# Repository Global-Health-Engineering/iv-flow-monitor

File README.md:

# Dripito — IV Drip Flow Monitor (Rev-B)

> Improving a low-cost intravenous infusion flow-rate monitoring device
> for paediatric care in humanitarian healthcare settings.
> ETH Zürich, Global Health Engineering — semester project, 2026.

A single-AA-cell IV drip monitor for resource-constrained clinical
environments. Custom STM32G0 PCB, optical dual-beam drop detection,
monochrome graphic LCD, piezo alarm, ASA-printed enclosure with
gear-driven broom-holder chamber clamp.

### → Full project page: **[gluflex.github.io/dripito](https://gluflex.github.io/dripito)**

Interactive dual-beam simulation, clickable PCB architecture, validation results, architecture decisions, assembly guide. This README covers only the essentials for cloning, building, and reproducing.

## At a glance

| | |
|---|---|
| **MCU** | STM32G071C8TX |
| **Hardware** | Rev-B PCB, KiCad 8.x, hand-assembled |
| **Detection** | Dual-beam optical, sphere-model volume calibration |
| **Power** | Single AA Li-ion via FFC, TPS610981 boost converter |
| **Enclosure** | ASA white FDM, sliding-gear chamber holder — Rev-B integrates the assembly for testing; full mechanical rework expected for Rev-C |
| **Validation** | 19 gravimetric-paired bench runs across 3 sessions (5 V_50 calibration + 11 position-drift + 3 raw-waveform-paired), macro-20 drip set; 7 raw-waveform captures total (4 unpaired warm-ups) |
| **BOM** | ~CHF 39, single-qty (see project page) |
| **Submission** | 2026-05-14 |

## Reproduce the analysis

One command, on a clean machine with Docker:

```bash
cd analysis/
docker compose up regenerate-figures-sample   # cold-clone test (sample data)
docker compose up regenerate-figures          # real campaign data
```

Pipeline source: [`analysis/notebooks/validation.ipynb`](analysis/notebooks/validation.ipynb).
Dependencies hash-locked in [`analysis/requirements.txt`](analysis/requirements.txt).
Protocol: [`docs/testing-and-validation.md`](docs/testing-and-validation.md).

## Build the firmware

1. Open `firmware/STM32CubeIDE/Dripito/` in STM32CubeIDE.
2. *Project → Build All*.
3. Connect ST-Link, *Run → Debug*.

Pin maps in [`firmware/README.md`](firmware/README.md).

## Hardware fabrication

PCB from `hardware/gerbers/` (JLCPCB / PCBWay).

Enclosure: STEP and STL exports in [`hardware/3dmodels/Enclosure/`](hardware/3dmodels/Enclosure/) (source CAD in Onshape). The current Rev-B enclosure is **not the final mechanical design** — it integrates the PCB + chamber holder + optics + battery into a testable assembly so the rest of the device can be validated. A full mechanical rework is expected for Rev-C. See [`docs/decisions/chamber-holder-mechanism.md`](docs/decisions/chamber-holder-mechanism.md), [`docs/decisions/sensor-arm-alignment.md`](docs/decisions/sensor-arm-alignment.md), and [`docs/enclosure-requirements.md`](docs/enclosure-requirements.md) for the rationale and Rev-C path.

## Repository layout

```
hardware/        KiCad 8.x project — schematic, PCB, libs, datasheets, gerbers, 3D models (PCB + Enclosure)
firmware/        STM32CubeIDE workspace (Dripito Rev-B)
enclosure/       Rev-B-is-not-final framing + cross-references; CAD lives in hardware/3dmodels/Enclosure/
docs/            Architecture decisions, requirements, results, limitations
data/            Raw validation CSVs, UART logs, gravimetric scale streams, geometry, edge cases
analysis/        Reproducible analysis pipeline (Docker + Jupyter) + diagnostic plotters + figures
tools/           Bench helpers (UART logging, scale logging, position-overlay rendering)
site/            GitHub Pages source (Astro)
media/           Photos, renders, demo clips
HANDOVER.md      State-of-the-prototype handover (Rev-B → Rev-C, what works / blockers / path)
CONTRIBUTING.md  Contribution guidelines (PRs paused during grading)
```

Each folder has its own `README.md`.

For the next person picking this up, start with [`HANDOVER.md`](HANDOVER.md): what works in Rev-B scope, the three blockers (position-dependence, drop-shape oscillation, tilt sensitivity), and the Rev-C optical-front-end path. [`docs/limitations.md`](docs/limitations.md) §17 is the matching architectural finding with bench evidence.

## Citation

A bachelor thesis preceded this work:

> Catarci, L. (2025). *Improving a Low-Cost Intravenous Infusion Flow-Rate Monitoring Device for Paediatric Care in Humanitarian Healthcare Settings*. ETH Zürich, Global Health Engineering. DOI: [10.5281/zenodo.16902366](https://doi.org/10.5281/zenodo.16902366).

The Rev-B work in this repository:

> Catarci, L. (2026). *Dripito — Open-Source IV Drip Flow Monitor (Rev-B)*. ETH Zürich, Global Health Engineering. DOI: [10.5281/zenodo.20199232](https://doi.org/10.5281/zenodo.20199232).

## License

- Code, firmware, docs, data: [CC BY 4.0](LICENSE-CC-BY-4.0.md)
- Hardware (KiCad project, custom symbols, most footprints): [CERN OHL 2.0 Permissive](LICENSE-CERN-OHL-2-PERMISSIVE.md)
- Three specific custom footprints: [CC BY-SA 4.0](LICENSE-CC-BY-SA-4.0.md) — see [`hardware/IV_Flow_Monitor_Footprints.pretty/README.md`](hardware/IV_Flow_Monitor_Footprints.pretty/README.md)
- CubeMX/HAL files retain `Copyright (c) STMicroelectronics` headers.

## Author and supervision

**Leandro Catarci** — MSc Mechanical Engineering, ETH Zürich. Semester project at ETH Global Health Engineering, 2026.

**Jakub Tkaczuk** — Supervisor.
**Prof. Elizabeth Tilley** — Group head, Chair of Global Health Engineering, ETH Zürich.

**Project originator:** Dr. Michelle Niescierenko — Boston Children's Hospital / Harvard Humanitarian Initiative.
**Clinical collaborator:** Dr. Janis Tupesis — University of Wisconsin / WHO Emergency Medical Teams.

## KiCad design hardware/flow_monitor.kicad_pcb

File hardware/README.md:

# hardware/

KiCad 8.x electronic design files for the Dripito monitor PCB —
schematic, board layout, project-local symbol and footprint libraries,
component datasheets, and fabrication outputs.

## Top-level files

| File | Purpose |
|------|---------|
| `flow_monitor.kicad_pro` | KiCad project file |
| `flow_monitor.kicad_sch` | Schematic |
| `flow_monitor.kicad_pcb` | Board layout |
| `sym-lib-table` | Registers `lib/IV_Flow_Monitor_Symbols.kicad_sym` |
| `fp-lib-table` | Registers `IV_Flow_Monitor_Footprints.pretty/` |
| `power_analysis.md` | Power-architecture analysis notes |

## Subdirectories

| Folder | Purpose |
|--------|---------|
| [`lib/`](lib/) | Project-local KiCad symbol libraries |
| [`IV_Flow_Monitor_Footprints.pretty/`](IV_Flow_Monitor_Footprints.pretty/) | Project-local KiCad footprint library |
| [`datasheets/`](datasheets/) | Component datasheets (PDFs) for everything on the BOM |
| [`gerbers/`](gerbers/) | Gerber + drill + pick-and-place fabrication outputs |
| [`3dmodels/`](3dmodels/) | 3D models (component STPs + assembled-board STEP exports) |
| [`scripts/`](scripts/) | Hardware-side automation (logo-to-footprint converter) |

## Gitignored paths

`flow_monitor-backups/` (KiCad timed snapshots), `temp/` (KiCad
scratch), `_autosave-*`, `fp-info-cache`.

## Workflow

- Open and build only via the **KiCad GUI** — no CLI build is configured.
- Hand-edits to `.kicad_sch` / `.kicad_pcb` (e.g. via scripts): always
  reopen in the KiCad GUI before committing — these files are sensitive
  to structural regressions that pass a text diff.
- New / copied symbols must have the project name in their `instances`
  block, or KiCad refuses to load them. Don't use `extends` inheritance
  across hierarchical `lib_symbols` blocks — flatten unit definitions.

## Licensing

- Three custom footprints are CC BY-SA 4.0 (see
  [`../LICENSE-CC-BY-SA-4.0.md`](../LICENSE-CC-BY-SA-4.0.md)):
  `SW_HYP_1TS005F-2500-5001`,
  `USB_C_Receptacle_GCT_USB4105-xx-A_16P_TopMnt_Horizontal`,
  `X_SW_Slide_SPDT_SSK12D07VG5`.
- All other hardware design files are CERN OHL 2.0 Permissive (see
  [`../LICENSE-CERN-OHL-2-PERMISSIVE.md`](../LICENSE-CERN-OHL-2-PERMISSIVE.md)).

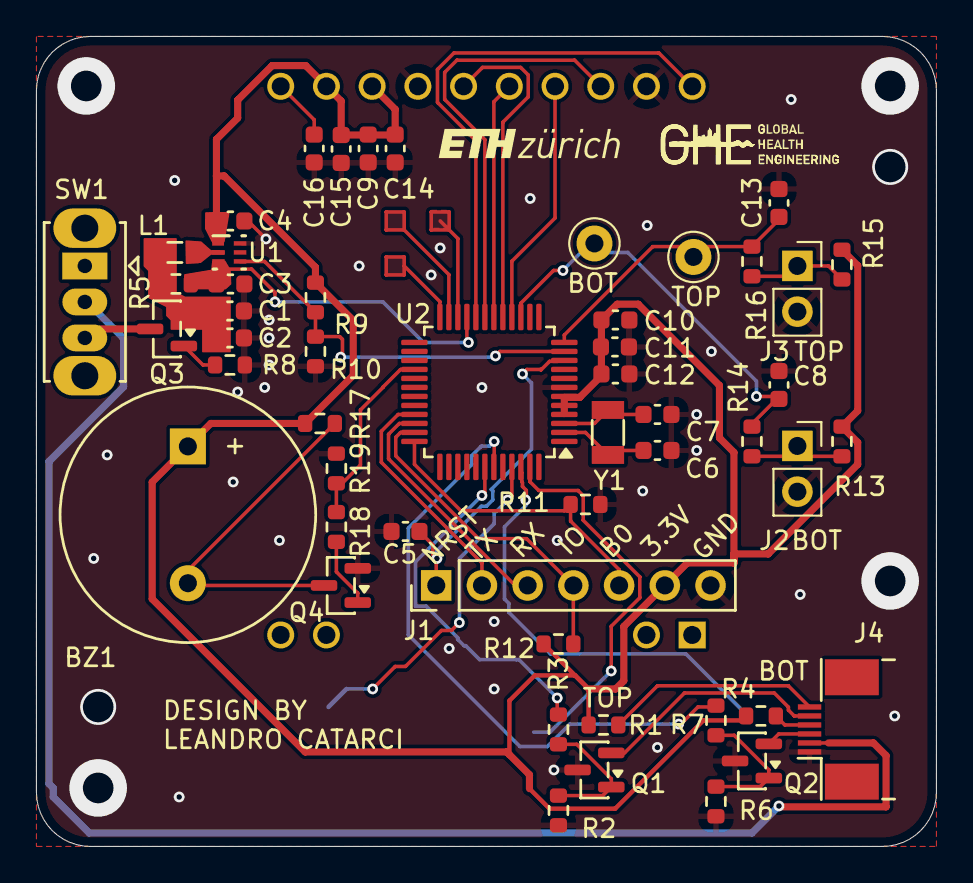
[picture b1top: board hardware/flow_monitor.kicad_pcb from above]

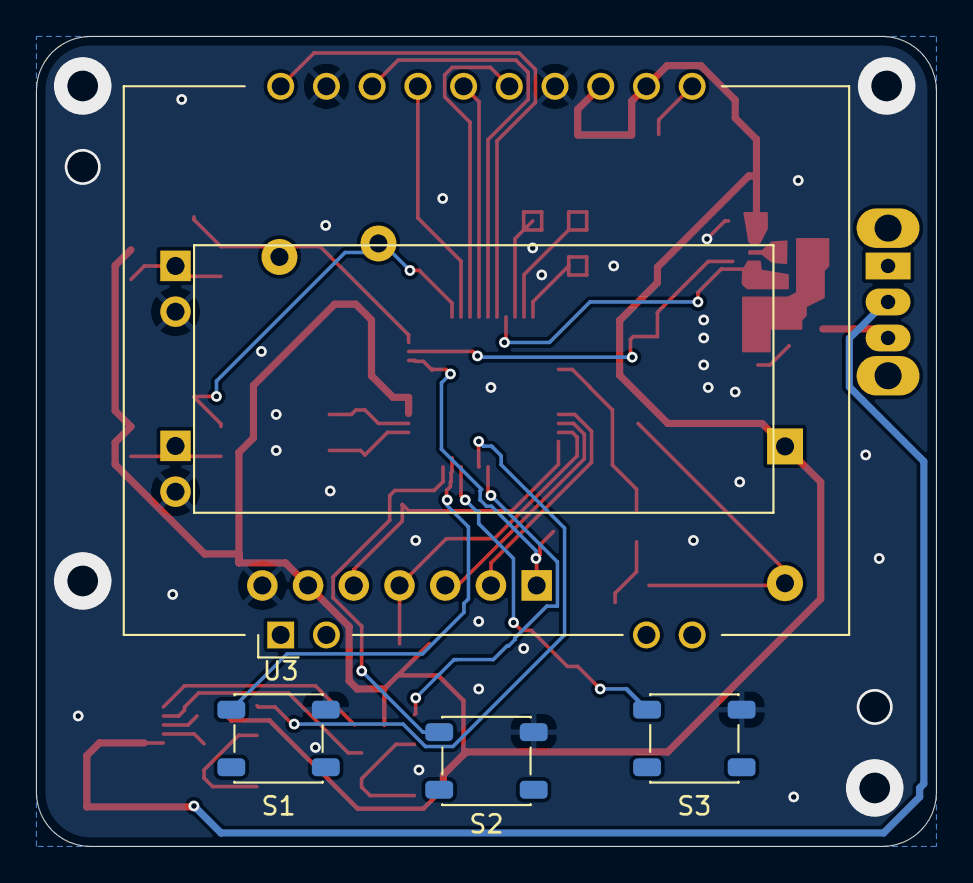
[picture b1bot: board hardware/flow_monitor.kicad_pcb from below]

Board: 2 copper layers, 50.0 x 45.0 mm, 55 parts (4 on the bottom side), 40 nets.

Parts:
BOT: TestPoint; TestPoint_Keystone_5000-5004_Miniature
BZ1: SFN-1407PA7.6; Buzzer_S&S_SFN-1407PA7.6
C1: 10uF; C_0603_1608Metric
C2, C3, C5, C14: 100nF; C_0603_1608Metric
C4: 22uF; C_0603_1608Metric
C6, C7: 20pF; C_0603_1608Metric
C8, C13: 100pF; C_0603_1608Metric
C9, C10, C12: 0.1uF; C_0603_1608Metric
C11: 1uF; C_0603_1608Metric
C15: 4700nF; C_0603_1608Metric
C16: 1000nF; C_0603_1608Metric
J1: Conn_01x07_Pin; PinHeader_1x07_P2.54mm_Vertical
J2: Conn_01x02_Socket_TOP; PinSocket_1x02_P2.54mm_Vertical
J3: Conn_01x02_Socket_BOT; PinSocket_1x02_P2.54mm_Vertical
J4: Conn_01x06_Socket; Jushuo_AFC07-S06FCA-00_1x6-1MP_P0.50_Horizontal
L1: 4.7uH; L_0805_2012Metric
Q1, Q2, Q4: 2N7002; SOT-23
Q3: AO3401A; SOT-23
R1, R3, R4, R7, R14, R16, R18: 100Ω; R_0603_1608Metric
R2, R6: 100kΩ; R_0603_1608Metric
R5: 390Ohm; R_0603_1608Metric
R8, R9, R10: 100k; R_0603_1608Metric
R11, R12, R19: 10kΩ; R_0603_1608Metric
R13, R15: 3.3kΩ; R_0603_1608Metric
R17: 1800Ω; R_0603_1608Metric
S1, S2, S3: PTS647SN38SMTR2_LFS; SW_SPST_PTS647_Sx38
SW1: SK12D07VG5; X_SW_Slide_SPDT_SSK12D07VG5
TP1: TestPoint; TestPoint_Keystone_5000-5004_Miniature
U1: TPS610981DSET; DSE0006A
U2: STM32G071C8Tx; LQFP-48_7x7mm_P0.5mm
U3: EA_DOGS164W-A; EA_DOGS164X-A
Y1: Crystal; Crystal_SMD_3215-2Pin_3.2x1.5mm

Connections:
+3.3V: BZ1.1 (+), C4.2, C9.1, C10.1, C11.2, C12.2, C14.1, C15.2, J1.6, R1.1, R4.1, R9.1, R12.1, R13.1, R15.1, R17.1, U1.1 (VMAIN), U2.4 (VBAT), U2.5 (VREF+), U2.6 (VDD), U3.12 (IM1), U3.13 (VDD)
/BUZZER_GATE: Q4.1 (G), R18.1
/LCD_VOUT: C16.2, U3.11 (VOUT)
/LED_GATE_BOT: Q2.1 (G), R6.2, R7.1
/LED_GATE_TOP: Q1.1 (G), R2.2, R3.1
/OSC32_IN: C6.2, U2.2 (PC14), Y1.2
/OSC32_OUT: C7.2, U2.3 (PC15), Y1.1
ADC_IR_DETECTOR_BOT: BOT.1, C8.2, R14.1, U2.15 (PA4)
ADC_IR_DETECTOR_TOP: C13.2, R16.1, TP1.1, U2.12 (PA1)
ADC_V_BAT: C3.2, R5.2, U1.3 (VIN), U2.21 (PB2)
BAT+: J4.2, SW1.2 (B)
BOOT0: J1.5, R11.1, U2.36 (PA14)
BST_MODE: R9.2, R10.1, U1.4 (MODE), U2.11 (PA0)
BST_SW: L1.2, U1.2 (SW)
BTN_MODE: S1.1 (NO), U2.46 (PB7)
BTN_MUTE: S3.1 (NO), U2.45 (PB6)
BTN_RES: S2.1 (NO), U2.47 (PB8)
BUZZER_CTRL: R18.2, R19.2, U2.28 (PA8)
BZ_DRN: BZ1.2 (-), Q4.3 (D), R17.2
GND: C1.2, C2.1, C3.1, C4.1, C5.2, C6.1, C7.1, C8.1, C9.2, C10.2, C11.1, C12.1, C13.1, C14.2, C15.1, C16.1, J1.7, J2.2, J3.2, J4.1, Q1.3 (D), Q2.3 (D), Q4.2 (S), R2.1, R6.1, R8.2, R10.2, R11.2, R19.1, S1.1 (NO), S2.1 (NO), S3.1 (NO), U1.6 (GND), U2.7 (VSS), U3.14 (VSS), U3.19 (SA0)
IR_LED_BOT+: J4.4, R4.2
IR_LED_BOT-: J4.3, Q2.2 (S)
IR_LED_TOP+: J4.6, R1.2
IR_LED_TOP-: J4.5, Q1.2 (S)
LCD_CS: U2.19 (PB0), U3.18 (CS)
LCD_MISO: U2.17 (PA6), U3.15 (SOD)
LCD_MOSI: U2.18 (PA7), U3.16 (SID)
LCD_RST: U2.20 (PB1), U3.20 (RST)
LCD_SCK: U2.16 (PA5), U3.17 (SCLK)
LED_CTRL_BOT: R7.2, U2.43 (PB4)
LED_CTRL_TOP: R3.2, U2.42 (PB3)
NRST: C5.1, J1.1, U2.10 (NRST)
PD_BIAS_BOT: J2.1, R13.2, R14.2
PD_BIAS_TOP: J3.1, R15.2, R16.2
RPOL_GATE: Q3.1 (G), R8.1
SWDIO: J1.4, R12.2, U2.35 (PA13)
UART1_RX: J1.3, U2.34 (PA10/PA12)
UART1_TX: J1.2, U2.33 (PA9/PA11)
VBAT_PROT: C1.1, C2.2, L1.1, Q3.2 (S), R5.1
VBAT_SW: Q3.3 (D), SW1.3 (C)

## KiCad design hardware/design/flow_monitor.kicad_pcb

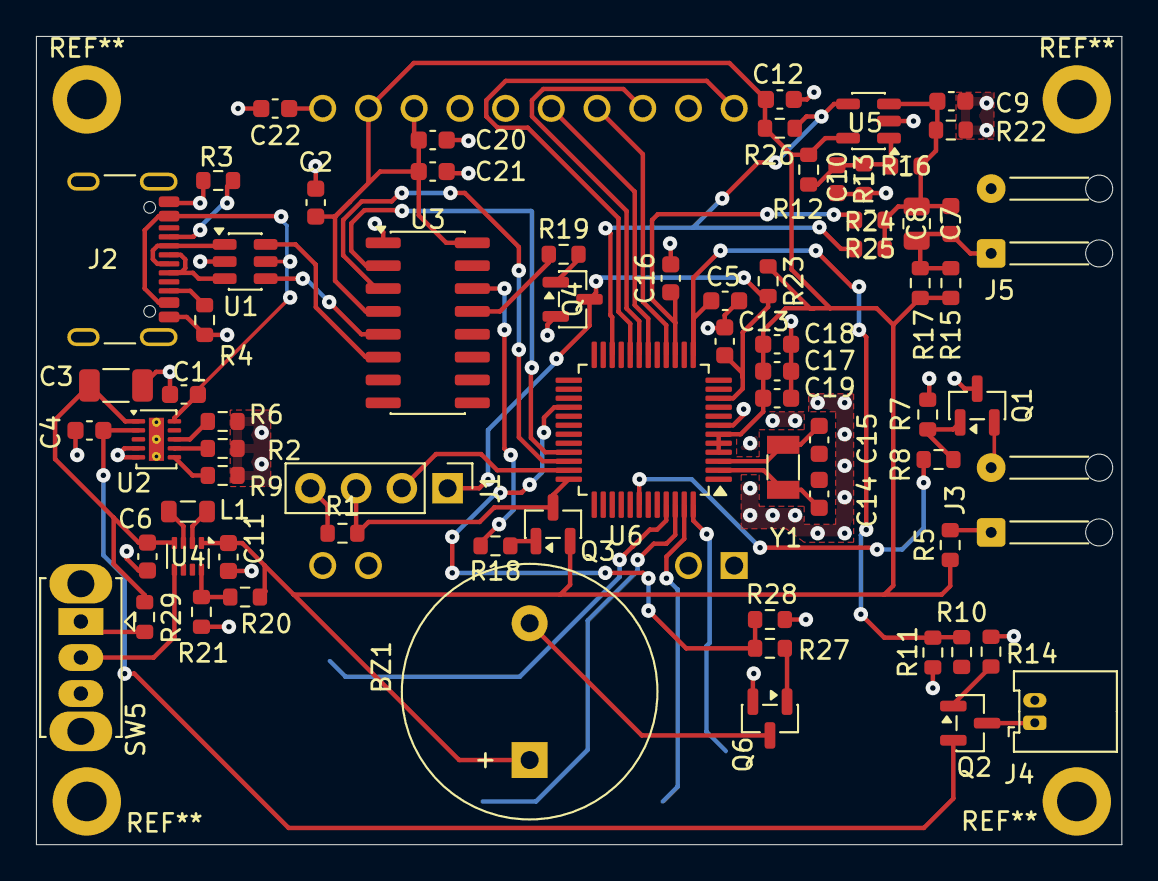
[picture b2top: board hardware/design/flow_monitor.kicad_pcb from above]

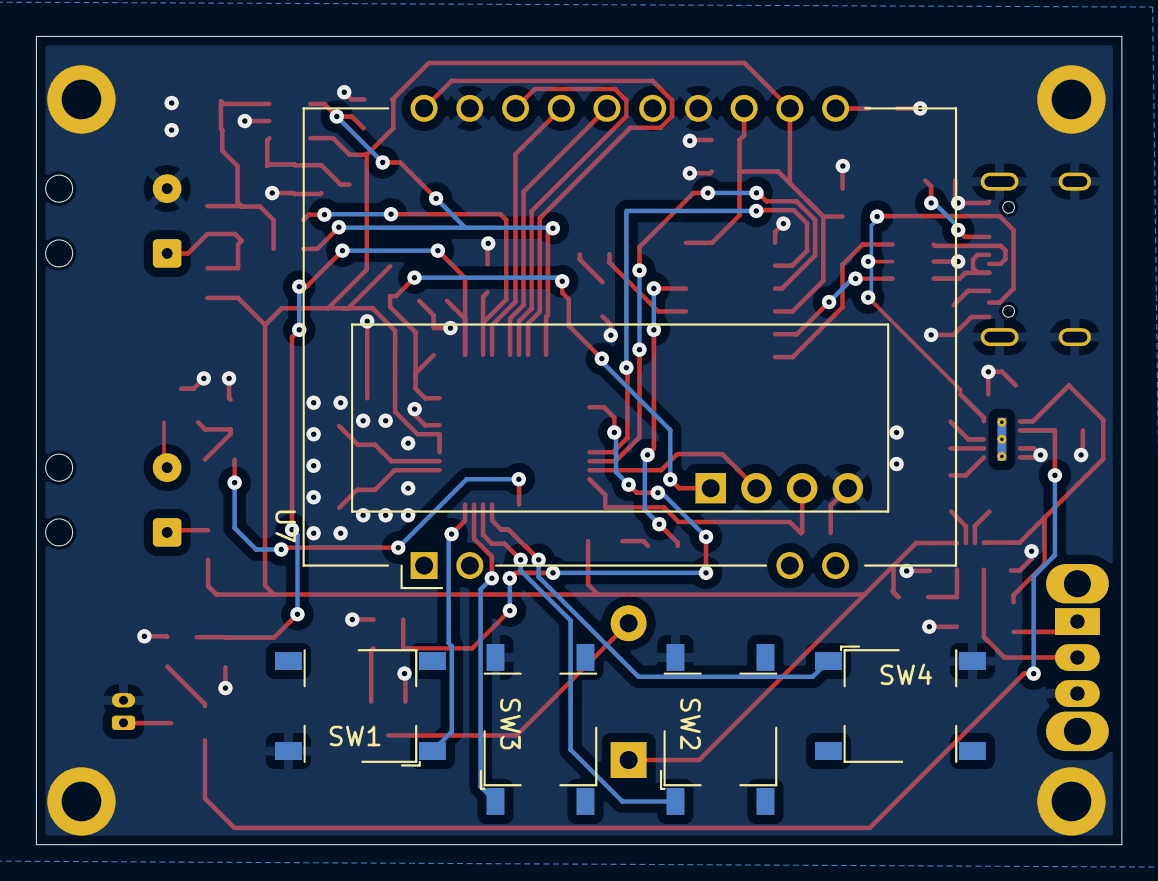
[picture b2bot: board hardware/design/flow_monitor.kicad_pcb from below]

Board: 2 copper layers, 60.3 x 44.9 mm, 76 parts (5 on the bottom side), 54 nets.

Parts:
BZ1: SFN-1407PA7.6; Buzzer_S&S_SFN-1407PA7.6
C1, C4: 1uF; C_0603_1608Metric
C2, C5, C7, C9, C10, C12, C16, C20: 100nF; C_0603_1608Metric
C3: 10uF; C_1206_3216Metric
C6, C11: 22uF; C_0603_1608Metric
C8: 4700nF; C_0805_2012Metric
C13, C17, C19: 0.1mF; C_0603_1608Metric
C14, C15: 20pF; C_0603_1608Metric
C18: 1mF; C_0603_1608Metric
C21: 4700nF; C_0603_1608Metric
C22: 1000nF; C_0603_1608Metric
J1: Conn_01x04_Pin; PinHeader_1x04_P2.54mm_Vertical
J2: USB_C_Receptacle_USB2.0_16P; USB_C_Receptacle_GCT_USB4105-xx-A_16P_TopMnt_Horizontal
J3, J5: Conn_01x02_Socket; SolderWire-0.1sqmm_1x02_P3.6mm_D0.4mm_OD1mm_Relief
J4: Conn_01x02_Socket; Molex_PicoBlade_53048-0210_1x02_P1.25mm_Horizontal
L1: 1uL; L_0805_2012Metric
Q1, Q6: 2N7002; SOT-23
Q2: IRLML6402; SOT-23
Q3: BC807; SOT-23
Q4: BC817; SOT-23
R1, R9, R14, R15, R18, R19, R23, R26, R28, R29: 10kΩ; R_0603_1608Metric
R2: 18kΩ; R_0603_1608Metric
R3, R4: 5.1kΩ; R_0603_1608Metric
R5, R8, R24, R27: 100Ω; R_0603_1608Metric
R6: 1kΩ; R_0603_1608Metric
R7: 100kΩ; R_0603_1608Metric
R10, R16, R22: 1MΩ; R_0603_1608Metric
R11: 500kΩ; R_0603_1608Metric
R12, R13: 47kΩ; R_0603_1608Metric
R17: 3.3kΩ; R_0603_1608Metric
R20: 511kΩ; R_0603_1608Metric
R21: 91kΩ; R_0603_1608Metric
R25: 330kΩ; R_0603_1608Metric
SW1, SW2, SW3, SW4: 1TS005F-2500-5001; SW_HYP_1TS005F-2500-5001
SW5: SW_SPDT; UNFINIDHED_SW_Slide_SPDT_SSK12D07VG5
U1: USBLC6-2SC6; SOT-23-6
U2: BQ25185DLHR; WSON-10-1EP_2x3mm_P0.5mm_EP0.84x2.4mm_ThermalVias
U3: CH340C; SOIC-16_3.9x9.9mm_P1.27mm
U4: TPS631000; SOT-583-8
U5: LMV331; SOT-23-5
U6: STM32G030C8Tx; LQFP-48_7x7mm_P0.5mm
U7: EA_DOGS164W-A; EA_DOGS104X-A
Y1: Crystal; Crystal_SMD_3215-2Pin_3.2x1.5mm

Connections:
+3.3V: BZ1.1 (+), C2.1, C11.2, C12.2, C17.1, C18.2, C19.2, C20.1, C21.2, Q3.2 (E), R5.1, R12.1, R15.1, R17.1, R20.1, R23.1, R26.1, U3.4 (V3), U3.16 (VCC), U4.1 (VOUT), U5.5 (V+), U6.4 (VBAT), U6.5 (VREF+), U6.6 (VDD), U7.12 (IM1), U7.13 (VDD)
+5V: C1.2, J2.A4 (VBUS), J2.A9 (VBUS), J2.B4 (VBUS), J2.B9 (VBUS), U1.5 (VBUS), U2.10 (IN)
/BAT+: J4.1, Q2.3 (D)
/BUZZER_GATE: Q6.1 (G), R27.1
/IR_LED+: J3.1, R5.2
/IR_LED-: J3.2, Q1.2 (S)
/LCD_VOUT: C22.2, U7.11 (VOUT)
/LED_GATE: Q1.1 (G), R7.2, R8.1
/OSC32_IN: C14.2, U6.2 (PC14), Y1.2
/OSC32_OUT: C15.2, U6.3 (PC15), Y1.1
/PD_AC: C7.1, C8.1, C9.2, R16.1, R22.1, R24.2, R25.1, U5.3 (-)
/PD_K: C7.2, C8.2, J5.1, R15.2, R17.2
/VREF = 1.65V: C10.2, R12.2, R13.1, R16.2, U5.1 (+)
ADC_IR_DETECTOR: C16.2, R24.1, U6.15 (PA4)
ADC_V_BAT: C5.1, R10.2, R11.1, U6.13 (PA2)
BOOT0: J1.3, Q3.3 (C), R1.1, U6.36 (PA14)
BTN_MINUS: SW1.1, U6.48 (PB9)
BTN_MODE: SW2.1, U6.46 (PB7)
BTN_MUTE: SW4.1, U6.45 (PB6)
BTN_PLUS: SW3.1, U6.47 (PB8)
BUZZER_CTRL: R27.2, R28.2, U6.28 (PA8)
DROP_INT: R25.2, R26.2, U5.4, U6.22 (PB10)
GND: C1.1, C2.2, C3.1, C4.1, C5.2, C6.1, C9.1, C10.1, C11.1, C12.1, C13.1, C14.1, C15.1, C16.1, C17.2, C18.1, C19.1, C20.2, C21.1, C22.1, J1.4, J2.A1 (GND), J2.A12 (GND), J2.B1 (GND), J2.B12 (GND), J2.SH, J4.2, J5.2, Q1.3 (D), Q4.2 (E), Q6.2 (S), R1.2, R2.1, R3.1, R4.2, R6.1, R7.1, R9.1, R11.2, R13.2, R14.2, R21.2, R22.2, R28.1, SW1.2, SW2.2, SW3.2, SW4.2, SW5.3 (C), U1.2 (GND), U2.4 (CE), U2.5 (GND), U3.1 (GND), U4.6 (MODE), U4.7 (GND), U5.2 (V-), U6.7 (VSS), U7.14 (VSS), U7.19 (SA0)
LCD_CS: U6.19 (PB0), U7.18 (CS)
LCD_MOSI: U6.18 (PA7), U7.16 (SID)
LCD_RST: U6.20 (PB1), U7.20 (RST)
LCD_SCK: U6.16 (PA5), U7.17 (SCLK)
LED_CTRL: R8.2, U6.42 (PB3)
NRST: C13.2, J1.1, Q4.3 (C), R23.2, U6.10 (NRST)
unnamed: BZ1.2 (-), Q6.3 (D)
unnamed: J2.A5 (CC1), R3.2
unnamed: J2.B5 (CC2), R4.1
unnamed: J2.A6 (D+), J2.B6 (D+), U1.3 (I/O2)
unnamed: J2.A7 (D-), J2.B7 (D-), U1.1 (I/O1)
unnamed: Q2.1 (G), R14.1
unnamed: C4.2, Q2.2 (S), R10.1, U2.2 (BAT)
unnamed: Q3.1 (B), R18.1
unnamed: Q4.1 (B), R19.2
unnamed: R29.1, SW5.1 (A)
unnamed: SW5.2 (B), U4.5 (EN)
unnamed: R2.2, U2.7 (ILIM/VSET)
unnamed: R6.2, U2.8 (ISET)
unnamed: C3.2, C6.2, R29.2, U2.1 (SYS), U4.4 (VIN)
unnamed: R9.2, U2.6 (TS/MR)
unnamed: R20.2, R21.1, U4.8 (FB)
unnamed: L1.1, U4.3 (LX1)
unnamed: L1.2, U4.2 (LX2)
SWDIO: J1.2, U6.35 (PA13)
UART1_RX: U3.3 (RXD), U6.34 (PA10/PA12)
UART1_TX: U3.2 (TXD), U6.33 (PA9/PA11)
UART_DTR: R19.1, U3.13 (~DTR)
UART_RTS: R18.2, U3.14 (~RTS)
USB_D+: U1.4 (I/O2), U3.5 (UD+)
USB_D-: U1.6 (I/O1), U3.6 (UD-)

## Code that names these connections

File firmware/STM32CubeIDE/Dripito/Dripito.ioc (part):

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Mcu.Name=STM32G071C(6-8-B)Tx
Mcu.Package=LQFP48
Mcu.UserName=STM32G071C8Tx
PA0.GPIOParameters=GPIO_Label
PA0.GPIO_Label=BST_MODE
PA0.Signal=GPIO_Output
PA1.GPIOParameters=GPIO_Label
PA1.GPIO_Label=ADC_IR_DETECTOR_TOP
PA1.Signal=SharedAnalog_PA1
PA10.GPIOParameters=GPIO_Label
PA10.GPIO_Label=UART1_RX
PA10.Mode=Asynchronous
PA10.Signal=USART1_RX
PA13.Mode=Serial_Wire
PA13.Signal=SYS_SWDIO
PA14-BOOT0.Mode=Serial_Wire
PA14-BOOT0.Signal=SYS_SWCLK
PA4.GPIOParameters=GPIO_Label
PA4.GPIO_Label=ADC_IR_DETECTOR_BOT
PA4.Mode=IN4
PA4.Signal=ADC1_IN4
PA5.GPIOParameters=GPIO_Label
PA5.GPIO_Label=LCD_SCK
PA5.Mode=Full_Duplex_Master
PA5.Signal=SPI1_SCK
PA6.GPIOParameters=GPIO_Label
PA6.GPIO_Label=LCD_MISO
PA6.Mode=Full_Duplex_Master
PA6.Signal=SPI1_MISO
PA7.GPIOParameters=GPIO_Label
PA7.GPIO_Label=LCD_MOSI
PA7.Mode=Full_Duplex_Master
PA7.Signal=SPI1_MOSI
PA8.GPIOParameters=GPIO_Label
PA8.GPIO_Label=BUZZER_CTRL
PA8.Signal=S_TIM1_CH1
PA9.GPIOParameters=GPIO_Label
PA9.GPIO_Label=UART1_TX
PA9.Mode=Asynchronous
PA9.Signal=USART1_TX
PB0.GPIOParameters=GPIO_Label
PB0.GPIO_Label=LCD_CS
PB0.Signal=GPIO_Output
PB1.GPIOParameters=GPIO_Label
PB1.GPIO_Label=LCD_RST
PB1.Signal=GPIO_Output
PB2.GPIOParameters=GPIO_Label
PB2.GPIO_Label=ADC_V_BAT
PB2.Mode=IN10
PB2.Signal=ADC1_IN10
PB3.GPIOParameters=GPIO_Label
PB3.GPIO_Label=LED_CTRL_TOP
PB3.Signal=S_TIM1_CH2
PB4.GPIOParameters=GPIO_Label
PB4.GPIO_Label=LED_CTRL_BOT
PB4.Signal=GPIO_Output
PB6.GPIOParameters=GPIO_PuPd,GPIO_Label
PB6.GPIO_Label=BTN_MUTE
PB6.GPIO_PuPd=GPIO_PULLUP
PB6.Signal=GPIO_Input
PB7.GPIOParameters=GPIO_PuPd,GPIO_Label
PB7.GPIO_Label=BTN_MODE
PB7.GPIO_PuPd=GPIO_PULLUP
PB7.Signal=GPIO_Input
PB8.GPIOParameters=GPIO_Label
PB8.GPIO_Label=BTN_RES
PB8.Signal=GPIO_Input
PC14-OSC32_IN\ (PC14).GPIOParameters=GPIO_Label
PC14-OSC32_IN\ (PC14).GPIO_Label=OSC32_IN
PC14-OSC32_IN\ (PC14).Mode=LSE-External-Oscillator
PC14-OSC32_IN\ (PC14).Signal=RCC_OSC32_IN
PC15-OSC32_OUT\ (PC15).GPIOParameters=GPIO_Label
PC15-OSC32_OUT\ (PC15).GPIO_Label=OSC32_OUT
PC15-OSC32_OUT\ (PC15).Mode=LSE-External-Oscillator
PC15-OSC32_OUT\ (PC15).Signal=RCC_OSC32_OUT
RCC.HSE_VALUE=8000000
RCC.SYSCLKFreq_VALUE=64000000
RCC.SYSCLKSource=RCC_SYSCLKSOURCE_PLLCLK
board=custom

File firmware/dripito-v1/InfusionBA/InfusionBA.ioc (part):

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Mcu.Name=STM32G030C(6-8)Tx
Mcu.Package=LQFP48
Mcu.UserName=STM32G030C8Tx
PA13.Mode=Serial_Wire
PA13.Signal=SYS_SWDIO
PA14-BOOT0.Mode=Serial_Wire
PA14-BOOT0.Signal=SYS_SWCLK
PA15.Mode=Asynchronous
PA15.Signal=USART2_RX
PA2.GPIOParameters=GPIO_Label
PA2.GPIO_Label=LOG_TX
PA2.Mode=Asynchronous
PA2.Signal=USART2_TX
PA3.GPIOParameters=GPIO_Label
PA3.GPIO_Label=PD_ADC
PA3.Mode=IN3
PA3.Signal=ADC1_IN3
PA4.Mode=IN4
PA4.Signal=ADC1_IN4
PA5.GPIOParameters=GPIO_Label
PA5.GPIO_Label=LCD_SCK
PA5.Mode=TX_Only_Simplex_Unidirect_Master
PA5.Signal=SPI1_SCK
PA7.GPIOParameters=GPIO_Label
PA7.GPIO_Label=LCD_MOSI
PA7.Mode=TX_Only_Simplex_Unidirect_Master
PA7.Signal=SPI1_MOSI
PA8.Signal=S_TIM1_CH1
PB0.GPIOParameters=GPIO_Speed,GPIO_PuPd,GPIO_Label,GPIO_ModeDefaultOutputPP
PB0.GPIO_Label=LCD_CS
PB0.GPIO_ModeDefaultOutputPP=GPIO_MODE_OUTPUT_PP
PB0.GPIO_PuPd=GPIO_PULLUP
PB0.GPIO_Speed=GPIO_SPEED_FREQ_HIGH
PB0.Signal=GPIO_Output
PB1.GPIOParameters=GPIO_Speed,GPIO_PuPd,GPIO_Label,GPIO_ModeDefaultOutputPP
PB1.GPIO_Label=LCD_RST
PB1.GPIO_ModeDefaultOutputPP=GPIO_MODE_OUTPUT_PP
PB1.GPIO_PuPd=GPIO_NOPULL
PB1.GPIO_Speed=GPIO_SPEED_FREQ_MEDIUM
PB1.Signal=GPIO_Output
PB10.GPIOParameters=GPIO_Label,GPIO_ModeDefaultEXTI
PB10.GPIO_Label=DROP_INT
PB10.GPIO_ModeDefaultEXTI=GPIO_MODE_IT_FALLING
PB10.Signal=GPXTI10
PB12.GPIOParameters=GPIO_Speed,PinState,GPIO_Label
PB12.GPIO_Label=BOOST_MODE_CTRL
PB12.GPIO_Speed=GPIO_SPEED_FREQ_MEDIUM
PB12.PinState=GPIO_PIN_SET
PB12.Signal=GPIO_Output
PB3.GPIOParameters=GPIO_Label
PB3.GPIO_Label=LED_CTRL
PB3.Signal=S_TIM1_CH2
PB6.GPIOParameters=GPIO_PuPd,GPIO_Label
PB6.GPIO_Label=BTN_MINUS
PB6.GPIO_PuPd=GPIO_PULLUP
PB6.Signal=GPIO_Input
PB7.GPIOParameters=GPIO_PuPd,GPIO_Label
PB7.GPIO_Label=BTN_PLUS
PB7.GPIO_PuPd=GPIO_PULLUP
PB7.Signal=GPIO_Input
PB8.GPIOParameters=GPIO_PuPd,GPIO_Label
PB8.GPIO_Label=BTN_MODE
PB8.GPIO_PuPd=GPIO_PULLUP
PB8.Signal=GPIO_Input
PB9.GPIOParameters=GPIO_PuPd,GPIO_Label
PB9.GPIO_Label=BTN_MUTE
PB9.GPIO_PuPd=GPIO_PULLUP
PB9.Signal=GPIO_Input
PC14-OSC32_IN\ (PC14).GPIOParameters=GPIO_Label
PC14-OSC32_IN\ (PC14).GPIO_Label=OSC32_IN
PC14-OSC32_IN\ (PC14).Mode=LSE-External-Oscillator
PC14-OSC32_IN\ (PC14).Signal=RCC_OSC32_IN
PC15-OSC32_OUT\ (PC15).GPIOParameters=GPIO_Label
PC15-OSC32_OUT\ (PC15).GPIO_Label=OSC32_OUT
PC15-OSC32_OUT\ (PC15).Mode=LSE-External-Oscillator
PC15-OSC32_OUT\ (PC15).Signal=RCC_OSC32_OUT
RCC.HSE_VALUE=8000000
RCC.SYSCLKFreq_VALUE=64000000
RCC.SYSCLKSource=RCC_SYSCLKSOURCE_PLLCLK
board=custom

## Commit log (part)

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2025-06-24 Add Altium IV_INFUSION_BA project files
2025-06-24 Add .gitignore to clean STM32CubeIDE and build files
2025-06-24 Fixed Logging (Hardware Issue: connect TX of Dripito with TX of ST-Link, NOT RX). Added Serial Logging for each button.
2025-06-25 Working Cursor Blinking
2025-08-03 fix(lcd): correct SPI nibble order and dial contrast • DOGS164 shows text now
2025-08-03 Resolve merge conflict: combine lcd.h and main.c
2025-08-03 Fixed Missing Functions
2025-08-03 Switch to external oscillator
2025-08-03 Set default target rate to 100 mL/h and add button hold
2025-08-03 Revert Back to old oscillator
2025-08-03 Fix button handling and flow simulation
2025-08-03 Implement flow and stop alarms with mute control
2025-08-04 Remove simulated drop and toggle display
2025-08-04 fixed press and hold on plus and minus button.
2025-08-04 Tried to fix battery, didn't work
2025-08-07 Deactivated Alarm
2025-08-19 Upload Analysis from Drive to Github
2026-02-18 cleanup
2026-02-27 final upload
2026-03-06 udpate doi
2026-03-14 Added MISO routing to LCD Screen
2026-03-20 add source and results at glance
2026-05-04 Add Rev-B hardware and firmware baseline
    - InfusionBA2: new STM32G071 project for Rev-B (dual photodiode, LPTIM1 Phase 2)
    - KiCad: Rev-B schematic + PCB (DOGS164, G071, TPS610981, COMP1 simplification)
    - Gerbers + STEP files from JLCPCB order W2026040304309275
    - Logo footprints (ETH, GHE) and generation script
    - Remove stale KiCad backup zips and lock files
2026-05-05 docs(testing): add pre-registered validation protocol
    Imports the EXP-0 through EXP-6 validation protocol from the working
    notes into the repository as a standalone, version-controlled document.
    This commit's timestamp serves as the pre-registration mark for the
    2026-05-07 → 2026-05-10 validation campaign — the protocol exists in
    git history before any official data is collected.
    Includes:
2026-05-05 docs(analysis): scaffold analysis/ with reproducibility contract
    Stub analysis/ with a README documenting the layout (notebooks/,
    figures/, scripts/), the pinning policy (requirements.in →
    requirements.txt via pip-compile, Dockerfile with digest-pinned base),
    and the reproducibility contract: a single command regenerates every
    figure from raw CSVs.
    Three reproduction paths documented for different audiences:
2026-05-05 docs(enclosure): add hand-off requirements spec for follow-up thesis
    Add docs/enclosure-requirements.md as a written specification for the
    3D-printed casing, pitched explicitly at a successor MSc/BSc student
    or a Rev-C revision. Captures *what the enclosure must do* once,
    durably, so the next revision does not re-derive these from clinical
    interviews and supplier catalogues.
    Sections:
2026-05-05 docs(media): document naming, formats, and what does not belong here
    Replace the one-line README with a useful one. Documents the naming
    convention (kebab-case for stable assets, YYYY-MM-DD prefix for dated
    shots, _render suffix to disambiguate renders from photos), format /
    resolution policy (max edge 2048 px, JPEG/PNG/MP4 by content type),
    and an explicit "what does not belong here" list.
    Specifically routes:
2026-05-07 chore(hardware): drop generated PCB and schematic review JSONs
2026-05-07 docs(testing): drop pre-registration framing, keep methodological discipline
2026-05-08 feat(led): drive LED_TOP at 100% duty
    Bump TIM1_CH2 compare from 125 (~50% duty) to 250 (compare > ARR=249,
    output always active). Equalises LED_TOP drive with LED_BOT (which is
    GPIO held HIGH = 100%) so steady-state ADC readings on the two channels
    become directly comparable for the asymmetry investigation logged in
    the journal entry today.
2026-05-12 feat(site): vendor Astro site source and add GitHub Pages deploy workflow
    Move the standalone Astro source from ../pages-astro/ into site/ so the
    GitHub Pages deploy runs from this repo. Workflow triggers on push to v2
    when site/** changes (plus workflow_dispatch). astro.config.mjs already
    targets gluflex.github.io/iv-flow-monitor-v2 — no config change needed.
    Post-merge, one manual step: Settings → Pages → Source → "GitHub Actions"
    to enable the deploy.
2026-05-14 fix(site): repoint every broken Pages link to real GitHub URLs
    The Pages site is an Astro single-page app under site/; it does not
    render docs/*.md. Every link to /docs/<anything>, every href="#"
    anchor, and the Decisions cards (pointing at a non-existent main
    branch) were 404. This commit repoints all of them to the GitHub
    blob/v2 / tree/v2 URLs that actually resolve. The two pages that
    genuinely don't exist (recommendations.html, external-reproducibility)
2026-05-14 feat(site): add Open Graph + Twitter Card + canonical + favicon
    The site shipped with bare title/description meta and no favicon.
    Sharing the URL on Slack/email/Twitter produced no preview. Adds
    absolute-URL canonical link, an SVG favicon, og:type/url/title/
    description/image/site_name, and matching Twitter summary_large_image
    tags. OG image reuses the existing PCB top render under site/public/pcb/.
2026-05-14 feat(site): make BOM groups collapsible (compact by default)
    Bill of materials previously rendered all 39 line items expanded —
    visually overwhelming for a glance. Now each group (Main PCB,
    Satellite breakout, Mechanical) collapses by default. Default view
    shows only the group headers, group subtotals, and the grand total
    (7 rows total). Clicking a group header expands or collapses just its
    line items; a new 'Expand all / Collapse all' pill in the header
2026-05-14 docs(analysis): drop AI-flavoured "the contract" sentence from README opener
    Sentence read as marketing rather than documentation; the section heading "Reproducing the analysis" already conveys the same idea without the rhetorical flourish.
2026-05-14 refactor(site): drop "Status" cell from Assembly manifest header
    Status meta-cell ("Bench-ready / Step N next / Build complete") was redundant — Steps counter + progress bar already convey the same state. Removes the third manifest cell, the related CSS, and the J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
2026-05-14 fix(site): Hero — drop stale STM32G0 + CHF 50 line, replace DOI badge with snapshot tag
    Third sentence ("Built on STM32G0, ≤ CHF 50 BOM target, deployable without an infusion pump") removed: STM32G0 is implementation detail that belongs in PCB section, and CHF 50 is the original target 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
2026-05-14 fix(site): PCB Hotspot 3 — Phase 1 LEDs are always-on continuous, not 8.3% duty
    Firmware confirms (main.c:395-398): TIM1_CH2 PWM at 100% duty for LED_TOP, static GPIO high for LED_BOT — both LEDs always on at ~21 mA each in Phase 1 active monitoring. The 8.3% / 150 µs / 1.80 ms 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
2026-05-14 chore(site): remove PowerTree component from PCB section
    PowerTree.astro had stale Li-ion AA framing, wrong Phase 1 duty (8.3 % → actually 100 %), and an aspirational ≥14 days runtime target that doesn't match any honest current number. The DualBeam.astro 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
2026-05-14 fix(site): use :global() for chime button so Astro doesn't hash the inner selector
    Previous fix .play-sound-slot button still got compiled to .play-sound-slot[data-astro-cid] button[data-astro-cid] — the inner button still required the scoping attribute, which the innerHTML-injecte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
2026-05-14 docs(results): tighten + honest-frame headline; cut drop-shape, op-envelope, V_50_05 sections
    Reframed headline: ±30 % per-run spread is far outside any clinical
    accuracy target — Rev-B is a dual-beam architecture demonstrator, not a
    clinically deployable monitor. Removed the "fundamental limit of the
    chord-time architecture" defence wording.
    Cut three sections that diluted the main story without adding load-bearing
    evidence: Architecture finding 3 (drop-shape oscillation deep-dive),
2026-05-14 chore(site): remove Pause/Step controls from DualBeam — sim auto-runs
    The Pause/Step controls in the DualBeam interactive existed mainly for
    debugging the per-drop animation. They cluttered the controls strip
    without serving the reader, who just wants to see the visualisation
    behave correctly at a chosen drip rate.
    Removed:
    - the two buttons from the controls strip
2026-05-14 docs(site): remove sanity-check bench figures from Analysis section
    Cumulative-mass and TOP-velocity-histogram figures were sanity-checks
    of the bench protocol, not findings of architectural significance.
    The architectural findings list right below already carries the
    analytical conclusions; the protocol-sanity panels added length
    without changing any reader's understanding of the device.
    Removed both figures plus the "figures below sanity-check the bench
2026-05-14 fix(site): let Reproducibility prose span the full panel width
    Removed the 70ch / 78ch max-width caps on .reproducibility p and
    .reproducibility p.repro-foot. The paragraphs were rendering as a narrow
    left-aligned column even though the panel container was wide, leaving a
    visually unbalanced right margin. Lines now run to the panel edge,
    matching the width of the <pre> code blocks.
2026-05-14 docs(site): relocate raw-waveform position figures to Analysis; drop confusing 3-session Bland-Altman
    Three changes:
    1. Cross-session Bland-Altman figure removed from Limitations §17.
    "One V_CAL_K, three sessions, one image" was technically the
    cleanest summary of position-dependence, but the n=737/n=150/n=51
    overlay with three different bias bands made the reader work too
    hard for the takeaway.
2026-05-14 feat(site): replace "Four paths" with "Continuation thesis topics" (5 cards + decision strip)
    Reframes Future Work from a strategic four-path narrative (Rev-C optics /
    firmware retry / clinical pilot / hand to next student) into five concrete
    1-semester thesis topics another student could pick up:
    T1 Mechanical — Casing & mounting redesign (folds in clip-on-used-sets
    + verticality-budget questions previously in Open Questions)
    T2 Software — Algorithm test bench (open-loop framework over the
2026-05-14 docs(limitations): disambiguate K range scope + add firmware constant refs
    Position-dependence (§17): K_fit varied 0.42-1.27 across four mount
    positions for the shipped mean-of-pulses algorithm (3x spread). Across
    all eight algorithm variants trialled in the afternoon, K_fit spanned
    0.42-1.98 (4.7x spread driven by mount geometry alone). Replaces
    the previous "0.28 to 1.27 across three different heights" framing,
    which mixed K_trialled with K_fit and undercounted the mount positions.
2026-05-14 docs(site): credit Niescierenko + Tupesis in Footer Acknowledgements
    Dr. Michelle Niescierenko (Boston Children's Hospital / Harvard
    Humanitarian Initiative) originated the Dripito project concept
    from clinical experience in humanitarian settings — the field use
    case (pediatric IV monitoring at flow rates where dose error
    matters) drove every architectural decision in this work.
    Dr. Janis Tupesis (University of Wisconsin / WHO Emergency Medical
2026-05-14 chore(site): drop Footer custom-footprints line + Hangar acknowledgement
    The "Three custom KiCad footprints under CC BY-SA 4.0" Footer line
    was true for the library carve-out but misleading on the rendered
    page: only one of the three (X_SW_Slide_SPDT_SSK12D07VG5) is
    actually placed on the Rev-B PCB. The other two
    (SW_HYP_1TS005F-2500-5001 alternate, USB_C_Receptacle_GCT_USB4105
    flagged in the library README as Rev-A legacy) are library
2026-05-15 docs: add minted Zenodo DOI 10.5281/zenodo.20199232 at TBD placeholders
    Pure ID swap — replaces "10.5281/zenodo.TBD — minted post-submission"
    with the concept DOI in the four files that carried the placeholder:
    CITATION.cff, README.md, docs/testing-and-validation.md, and
    site/src/components/Footer.astro. Adds the standard Zenodo DOI badge
    in the two display locations (README badge row, Footer cite line).
    No content, wording, or structural changes beyond the ID itself.
